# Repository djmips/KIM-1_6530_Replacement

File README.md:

"# KIM-1_6530_Replacement" 

Forked from https://github.com/CorshamTech/KIM-1_6530_Replacement

Project now archived as of October 2024 at http://retro.hansotten.nl/corsham-projects-archive/kim-1-products/kim-1-6530-replacement-board/

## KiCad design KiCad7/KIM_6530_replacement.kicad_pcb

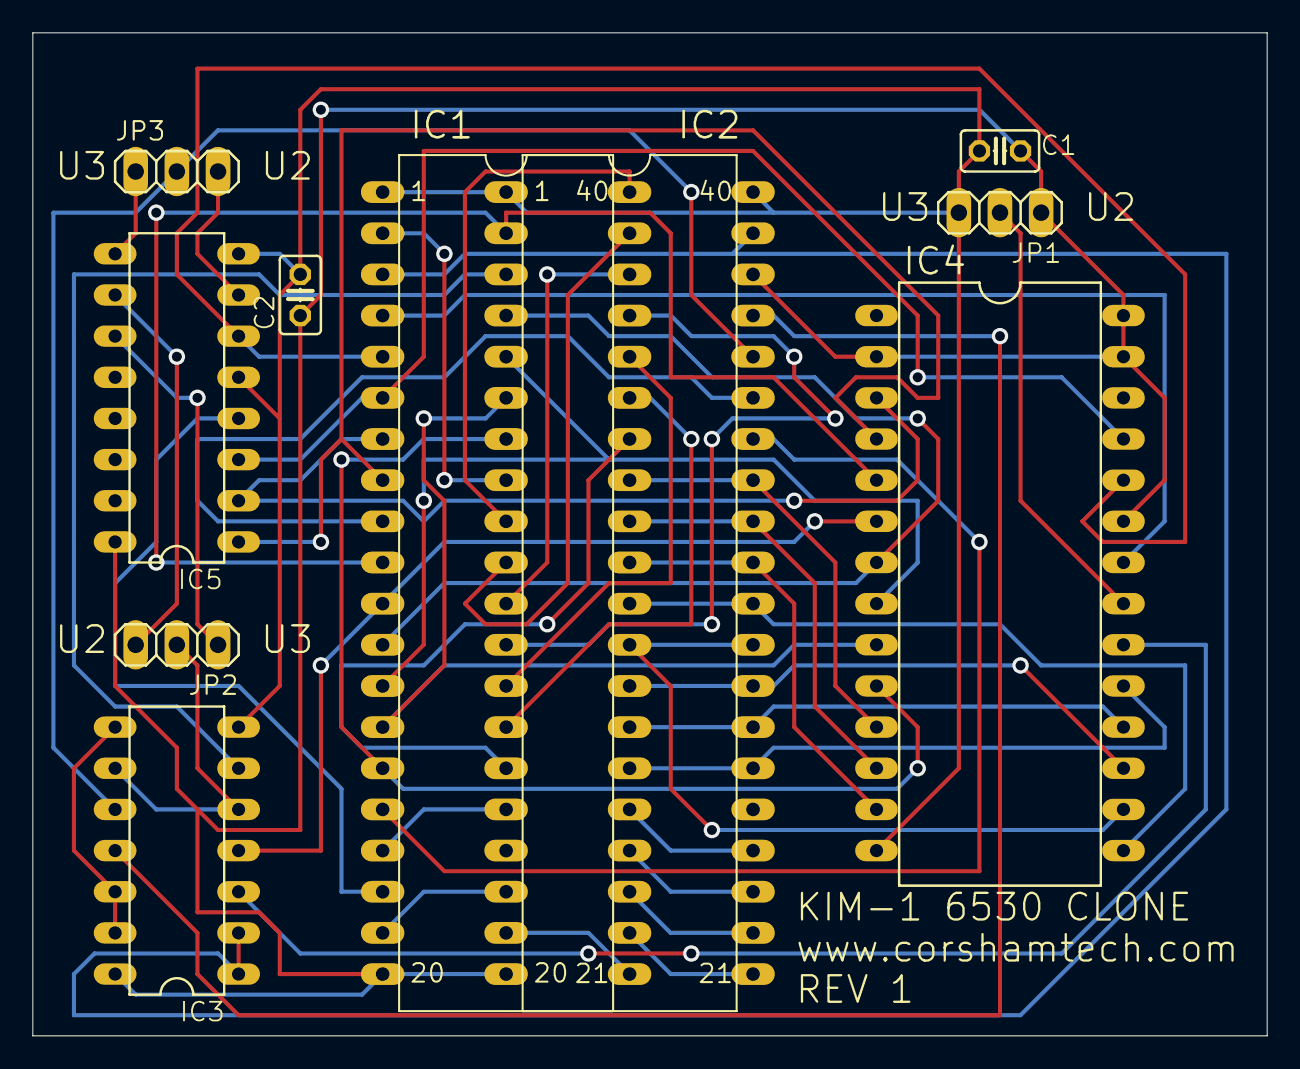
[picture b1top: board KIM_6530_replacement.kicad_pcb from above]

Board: 2 copper layers, 76.2 x 61.9 mm, 10 parts (0 on the bottom side), 51 nets.

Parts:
C1, C2: .1; C025-025X050
IC1: 6530-KIM; DIP40
IC2: 6532; DIP40
IC3: 74LS00N; DIL14
IC4: 28C64AP; DIL28-6
IC5: 74LS138N; DIL16
JP1: EPROM; 1X03
JP2, JP3: 1X03

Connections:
A0: IC1.15, IC2.7, IC4.10
A1: IC1.14, IC2.6, IC4.9
A2: IC1.13, IC2.5, IC4.8
A3: IC1.12, IC2.4, IC4.7
A4: IC1.11, IC3.4, IC4.6
A4_ADJ: IC2.3, IC3.6
A5: IC1.10, IC2.2, IC4.5
A6: IC1.8, IC4.4, IC5.1
A7: IC1.7, IC4.3, IC5.2
A8: IC1.6, IC4.25, IC5.3
A9: IC1.5, IC4.24, IC5.6
A10: IC4.21, JP1.2
D0: IC1.33, IC2.33, IC4.11
D1: IC1.32, IC2.32, IC4.12
D2: IC1.31, IC2.31, IC4.13
D3: IC1.30, IC2.30, IC4.15
D4: IC1.29, IC2.29, IC4.16
D5: IC1.28, IC2.28, IC4.17
D6: IC1.27, IC2.27, IC4.18
D7: IC1.26, IC2.26, IC4.19
GND: C1.2, C2.2, IC1.1, IC2.1, IC2.40, IC3.7, IC4.14, IC5.5, IC5.8, JP1.3
unnamed: IC1.2, IC2.8
unnamed: IC1.40, IC2.9
unnamed: IC1.39, IC2.10
unnamed: IC1.38, IC2.11
unnamed: IC1.37, IC2.12
unnamed: IC1.36, IC2.13
unnamed: IC1.35, IC2.14
unnamed: IC1.34, IC2.15
unnamed: IC1.25, IC2.24
unnamed: IC1.24, IC2.23
unnamed: IC1.23, IC2.22
unnamed: IC1.22, IC2.21
unnamed: IC1.21, IC2.19
unnamed: IC1.19, IC2.18
unnamed: IC1.17, IC2.16
unnamed: IC1.16, IC2.34
ON_6532: IC3.8, IC3.12, IC3.13
PH2: IC1.3, IC2.39, IC3.1, IC3.2
R/~W: IC1.9, IC2.35
VCC: C1.1, C2.1, IC1.20, IC2.20, IC2.38, IC3.14, IC4.2, IC4.23, IC4.27, IC4.28, IC5.16, JP1.1
~K5: IC1.18, IC5.4
~ON_6532: IC2.37, IC3.11
~PH2: IC3.3, IC4.20
~RAM_SELECT: IC2.36, IC3.10, JP3.2
~REGISTER_SELECT: IC3.5, IC3.9, JP2.2
~ROM_SELECT: IC1.4, IC4.22
~S_17C0: IC5.7, JP3.3
~S_1700: IC5.11, JP2.1
~S_1740: IC5.10, JP2.3
~S_1780: IC5.9, JP3.1

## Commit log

2024-10-03 Bob Applegate's EAGLE project.
2024-10-03 KiCad Conversion
